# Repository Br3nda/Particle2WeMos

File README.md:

Particle Spark/Photon to WeMos Adapter
======================================

This adapter is used to put in place of a Spark/Photon a WeMos board with ESP8266 I needed for a specific French [project][3]. I needed SPI for RFM69 Module with IRQ on ~~GPIO2~~ GPIO15 and SS on GPIO2 (see below why).
I choosed ~~NodeMCU~~ WeMos boards instead of ESP8266 because they have all I need on board, such as pullups, switches, USB power, 3/3V regulator, USB2Serial... You can find more information on WeMos [site][1] that is really well documented.
WeMos board are now used instead of NodeMCU's one because they're just smaller, features remains the same, but I also suspect WeMos regulator far better quality than the one used on NodeMCU that are just fake of originals AMS117 3V3.

Since ESP8266 has less pin than Particle boards, only "classic" have been connected

- SPI Interface (GPIO12 to 14) GPIO15 is used for RFM69 IRQ
- I2C Interface (GPIO14 and GPIO5)
- Serial (GPIO1 and GPIO3)
- GPIO0 as free I/O (Flash button on NodeMCU)
- GPIO2 is used as Chip Select (SS) for RFM69
- GPIO16 as free I/O (LED and KEY on NodeMCU)

To boot correctly ESP8266 needs some pins at defined level, GPIO15 must be LOW and GPIO2 must be HIGH. Unfortunatlly with RFM69 connected as IRQ to GPIO2 and SS to GPIO15 it does not boot because RF69 pull it DIO IRQ to LOW, making GPIO2 LOW and ESP8266 not booting. The fix is to reverse the wiring, connect IRQ to GPIO15 and SS to GPIO2 (and do according changes in the code). 
- Teleinfo had some issue due to NodeMCU USB/Serial onboard converter that was in conflict and was killing RX signal coming from optocoupler. To avoid this I've put 2 inverters to have a correct RX Teleinfo signal coming to EMP8266. No Risk because on board RX Signal of WeMos has a 470 Ohm resistor in serial of this line. To avoid this may be we could use a ESP8266 without any USB/Serial adapteur such as a Adafruit [Huzzah][5], Olimex [ESP8266 Dev][6] or even [OAK][6]
- to be able to handle all Remora PCB version I added the feature to enable/disable Téléinfo FET Staging (they will already be placed on Remora V1.3 PCB) using Jumper J1 & J2.

*Boards are ordered as testing from OSHPark, I did not fully tested them yet, I will update as soon has I got them in my hands. Use at your own risks*

Detailed Description
====================

Look at the schematics for more informations.

### Schematic  

### Boards  
&nbsp;
&nbsp; 

You can order the PCB of this board v1.0 at [OSHPARK][4]

### Assembled boards

I'm currently waiting for boards from OSHPARK

##License

You can do whatever you like with this design.

##Misc
See news and other projects on my [blog][2] 
 
[1]: http://www.wemos.cc/wiki/doku.php?id=en:d1_mini
[2]: https://hallard.me
[3]: https://github.com/thibdct/programmateur-fil-pilote-wifi/tree/master/Logiciel/remora
[4]: https://oshpark.com/shared_projects/5sAC9l7e
[5]: https://www.adafruit.com/product/2471
[6]: https://www.olimex.com/Products/IoT/MOD-WIFI-ESP8266-DEV/
[7]: http://digistump.com/products/145

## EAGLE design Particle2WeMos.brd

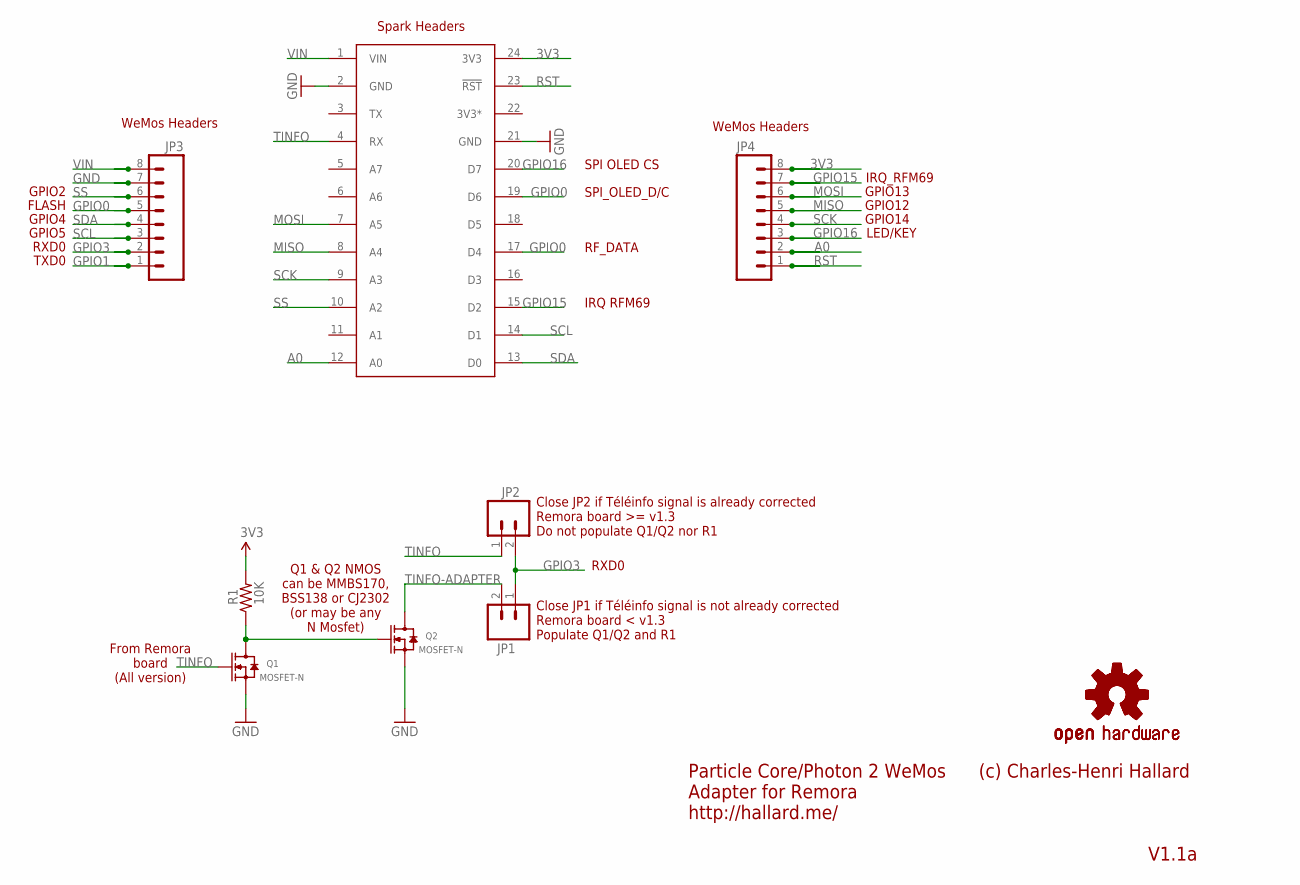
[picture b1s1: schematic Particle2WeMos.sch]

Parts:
JP1, JP2: M02LOCK; 1X02_LOCK
JP3, JP4: M08SILK_FEMALE_PTH; 1X08
LOGO1, LOGO2: OSHW-LOGOM; OSHW-LOGO-M
Q1, Q2: MOSFET-N; SOT23
R1: 10K; 0805-RES
U$2: SPARK_CORECORE; SPARK_CORE

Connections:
3V3: JP4.8, R1.2, U$2.24 (3V3)
3V3*: U$2.22 (3V3*)
A0: JP4.2, U$2.12 (A0)
GND: JP3.7, Q1.2 (S), Q2.2 (S), U$2.2 (GND), U$2.21 (GND)
GPIO0: JP3.5, U$2.17 (D4), U$2.19 (D6)
GPIO1: JP3.1
GPIO3: JP1.1, JP2.2, JP3.2
GPIO15: JP4.7, U$2.15 (D2)
GPIO16: JP4.3, U$2.20 (D7)
MISO: JP4.5, U$2.8 (A4)
MOSI: JP4.6, U$2.7 (A5)
unnamed: Q1.3 (D), Q2.1 (G), R1.1
RST: JP4.1, U$2.23 (!RST)
SCK: JP4.4, U$2.9 (A3)
SCL: JP3.3, U$2.14 (D1)
SDA: JP3.4, U$2.13 (D0)
SS: JP3.6, U$2.10 (A2)
TINFO: JP2.1, Q1.1 (G), U$2.4 (RX)
TINFO-ADAPTER: JP1.2, Q2.3 (D)
VIN: JP3.8, U$2.1 (VIN)

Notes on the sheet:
WeMos Headers
IRQ RFM69
SPI_OLED_D/C
SPI OLED CS
RF_DATA
Spark Headers
Particle Core/Photon 2 WeMos Adapter for Remora http://hallard.me/
(c) Charles-Henri Hallard
V1.1a
RXD0
Q1 & Q2 NMOS can be MMBS170, BSS138 or CJ2302 (or may be any N Mosfet)
Close JP1 if Téléinfo signal is not already corrected Remora board < v1.3 Populate Q1/Q2 and R1
Close JP2 if Téléinfo signal is already corrected Remora board >= v1.3 Do not populate Q1/Q2 nor R1
From Remora board (All version)
GPIO2
FLASH
GPIO12
GPIO4
GPIO5
TXD0
GPIO13
GPIO14
IRQ_RFM69
LED/KEY

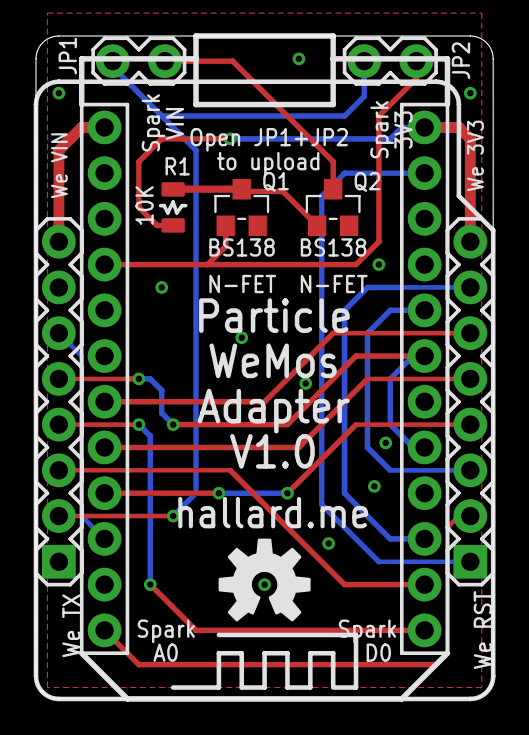
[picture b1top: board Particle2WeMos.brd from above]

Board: 2 copper layers, 25.4 x 36.8 mm, 10 parts (1 on the bottom side), 18 nets.

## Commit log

2016-01-16 :confetti_ball: Added .gitattributes
2016-01-16 Creation
2016-01-16 Added oshpark and wemos links
2016-01-16 Corrected OSHPark link

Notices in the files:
parts and their libraries:
SparkFun-Connectors: Licensing: Creative Commons ShareAlike 4.0 International - https://creativecommons.org/licenses/by-sa/4.0
